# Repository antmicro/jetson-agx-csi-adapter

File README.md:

# Antmicro Jetson AGX CSI Adapter

Copyright (c) 2022-2024 [Antmicro](https://www.antmicro.com)

## Overview
This project contains hardware design files for a CSI camera adapter designed to be used with Nvidia Jetson AGX platform devkits (Orin, Xavier).
It separates the camera module interface connector into two 50-pin flat cable connectors, which are compatible with a variety of video accessories developed by Antmicro.
 
## Project structure
The main directory contains KiCad PCB project files, a LICENSE, and a README.
The remaining files are stored in the following directories:

* `img` - contains graphics for this README
* `doc` - contains generated schematics and other documentation
* `assets` - contains visual assets for showcasing this design on [Open Hardware Portal](https://openhardware.antmicro.com)

## Key features
* Nvidia Camera Module Connector compatible with Jetson AGX Orin and Jetson Xavier AGX devkits,
* Two Antmicro CSI Connectors (2x 4-lane MIPI CSI-2 or 4x 4-lane MIPI CSI-2)
* I2C multiplexer for connecting multiple cameras to separate I2C interfaces
* On-board DC-DC converter to power the cameras
* Simple frame synchronization circuitry
* QWIIC connector for external sensors
* Liquid lens connector for I2C-controlled liquid lenses

The camera connectors are electrically compatible with several video accessories created by Antmicro, such as:
 
* [Antmicro - Alvium flexible CSI adapter](https://github.com/antmicro/alvium-flexible-csi-adapter)
* [OV9281 Dual Camera Board](https://github.com/antmicro/ov9281-camera-board)
* [SDI-MIPI bridge](https://github.com/antmicro/sdi-mipi-bridge)
* [HDMI-MIPI bridge](https://github.com/antmicro/hdmi-mipi-bridge)

## License
This project is published under the [Apache-2.0](LICENSE) license.

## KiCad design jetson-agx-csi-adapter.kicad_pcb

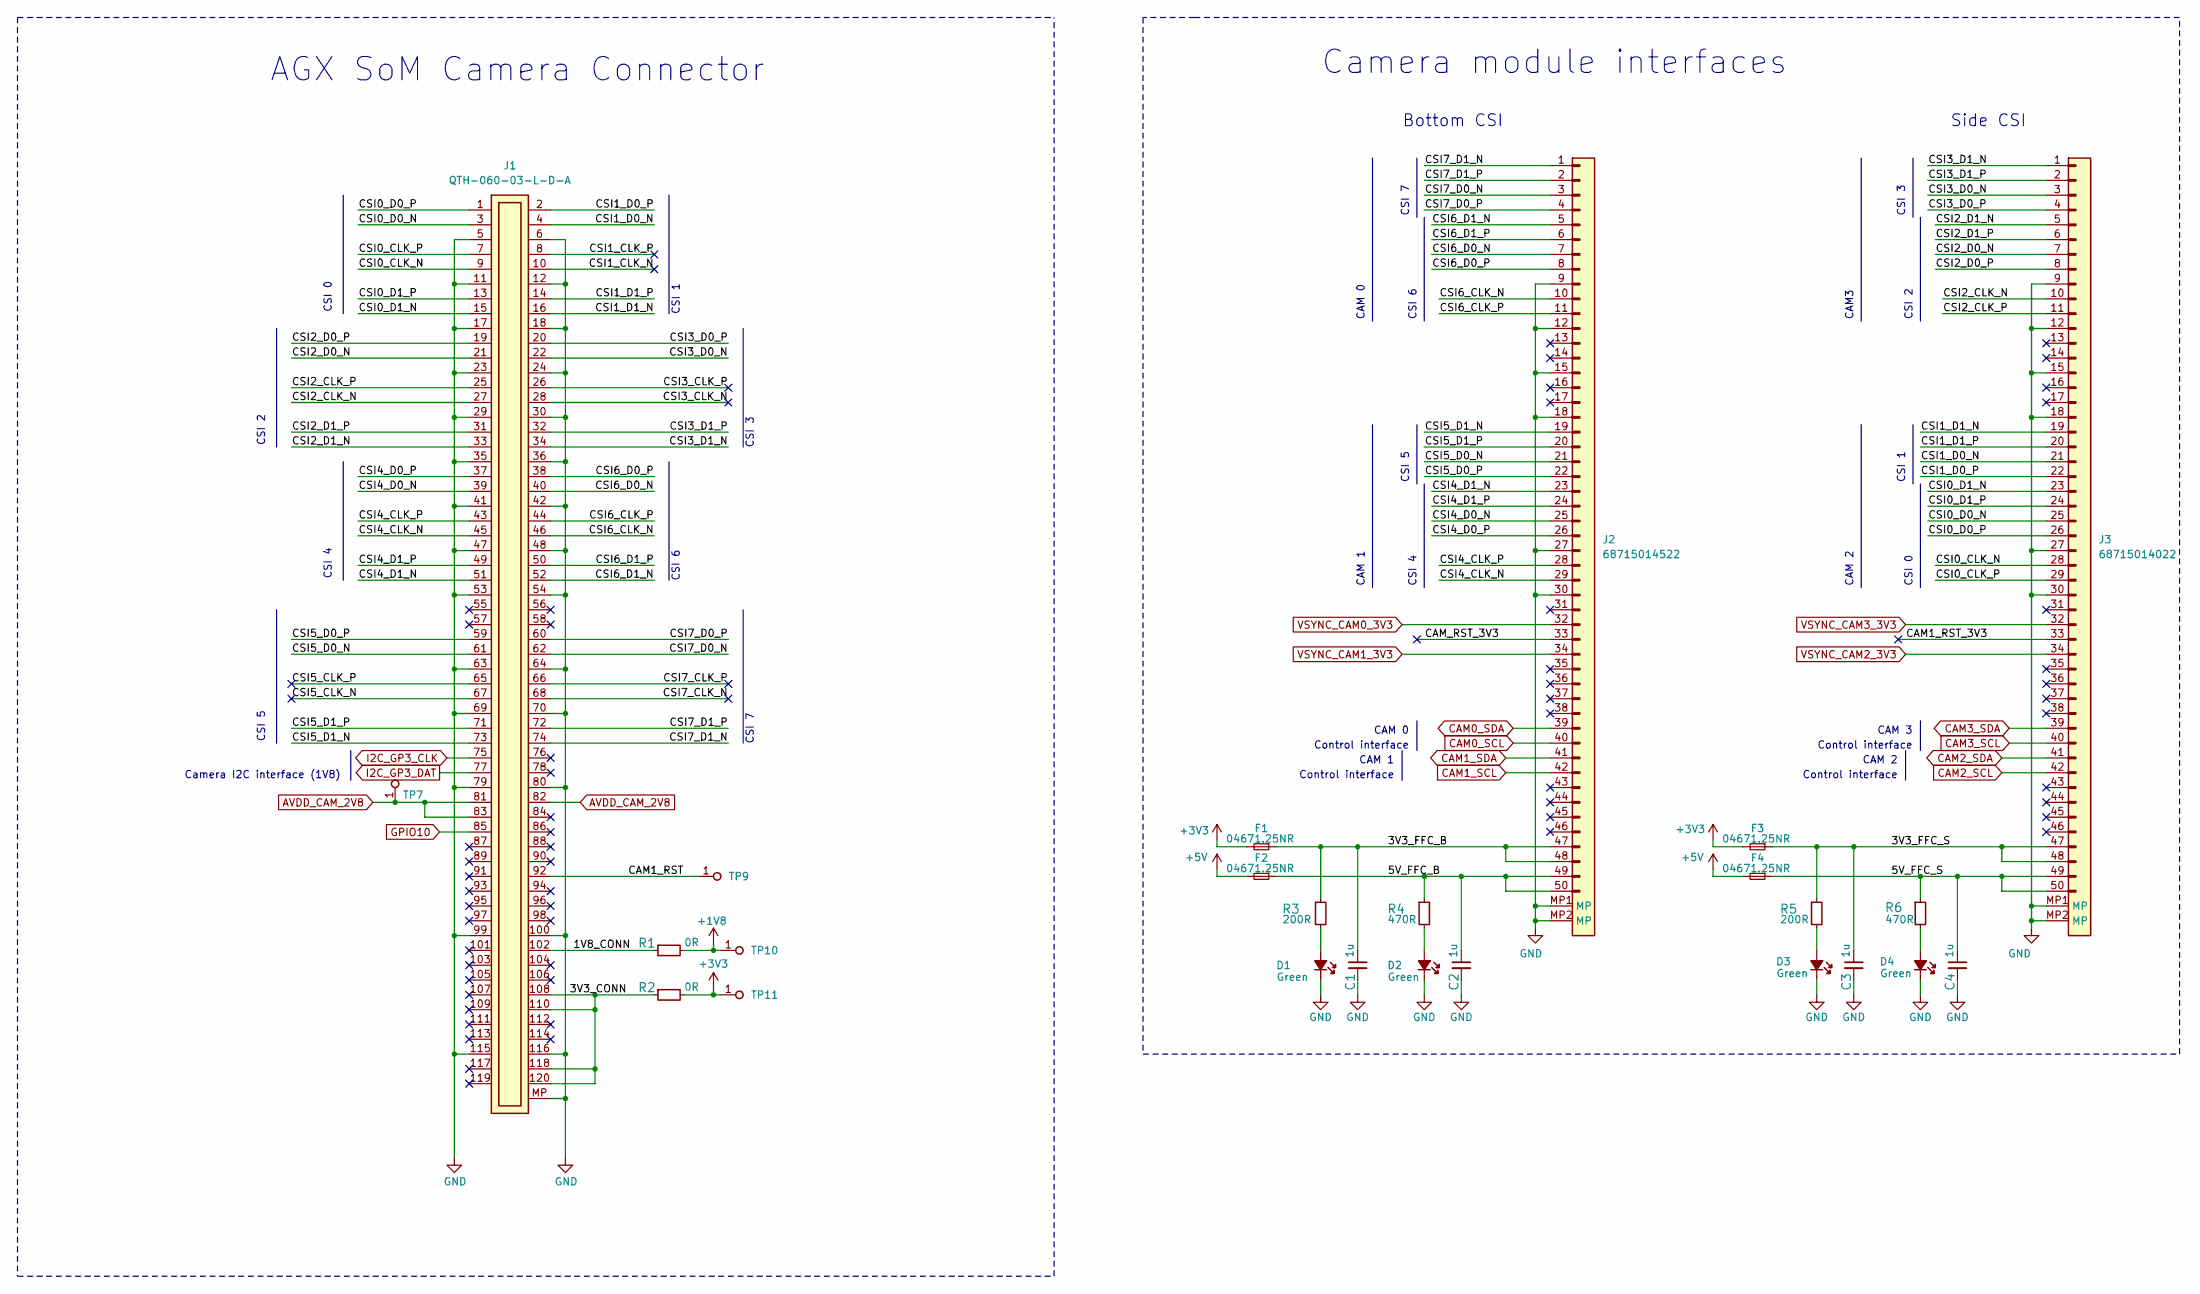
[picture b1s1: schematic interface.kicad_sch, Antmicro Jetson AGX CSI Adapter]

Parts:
C1, C2, C3, C4: C_1u_0603; C_0603_1608Metric; MPN 0603YD105KAT2A
D1, D2, D3, D4: LED_G_0603_LTST-C190GKT; LED_0603_1608Metric_G; MPN LTST-C190GKT
F1, F2, F3, F4: F_1.25A_0603; F_0603_1608Metric; MPN 04671.25NR
J1: Plug_Samtec_QTH_2x60_QTH-060-03-L-D-A; Conn_Plug_Samtec_QTH_2x60_QTH-060-03-L-D-A; MPN QTH-060-03-L-D-A
J2: Conn_FFC_WE_68715014522; Conn_FFC_WE_68715014x22; MPN 68715014522
J3: Conn_FFC_WE_68715014022_CUSTOM_FLIPPED; Conn_FFC_WE_68715014x22_CUSTOM_FLIPPED; MPN 68715014022
R1, R2: R_0R_0805; R_0805_2012Metric; MPN CRCW08050000Z0EA
R3, R5: R_200R_0402; R_0402_1005Metric; Tolerance 1%; MPN CR0402-FX-2000GLF
R4, R6: R_470R_0402; R_0402_1005Metric; Tolerance 1%; MPN CR0402-FX-4700GLF
TP7, TP9, TP10, TP11: TP_0.75mm_SMD; TP_SMD_0.75mm

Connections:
+1V8: R1.2, TP10.1; also elsewhere on the board
+3V3: F1.2, F3.2, R2.2, TP11.1; also elsewhere on the board
+5V: F2.2, F4.2; also elsewhere on the board
/Interface/1V8_CONN: J1.102, R1.1
/Interface/3V3_CONN: J1.108, J1.110, J1.118, J1.120, R2.1
/Interface/3V3_FFC_B: C1.1, F1.1, J2.47, J2.48, R3.1
/Interface/3V3_FFC_S: C3.1, F3.1, J3.47, J3.48, R5.1
/Interface/5V_FFC_B: C2.1, F2.1, J2.49, J2.50, R4.1
/Interface/5V_FFC_S: C4.1, F4.1, J3.49, J3.50, R6.1
/Interface/CAM1_RST: J1.92, TP9.1
/Interface/CAM1_RST_3V3: J3.33
/Interface/CAM_RST_3V3: J2.33
/Interface/CSI0_CLK_N: J1.9, J3.28
/Interface/CSI0_CLK_P: J1.7, J3.29
/Interface/CSI0_D0_N: J1.3, J3.25
/Interface/CSI0_D0_P: J1.1, J3.26
/Interface/CSI0_D1_N: J1.15, J3.23
/Interface/CSI0_D1_P: J1.13, J3.24
/Interface/CSI1_CLK_N: J1.10
/Interface/CSI1_CLK_P: J1.8
/Interface/CSI1_D0_N: J1.4, J3.21
/Interface/CSI1_D0_P: J1.2, J3.22
/Interface/CSI1_D1_N: J1.16, J3.19
/Interface/CSI1_D1_P: J1.14, J3.20
/Interface/CSI2_CLK_N: J1.27, J3.10
/Interface/CSI2_CLK_P: J1.25, J3.11
/Interface/CSI2_D0_N: J1.21, J3.7
/Interface/CSI2_D0_P: J1.19, J3.8
/Interface/CSI2_D1_N: J1.33, J3.5
/Interface/CSI2_D1_P: J1.31, J3.6
/Interface/CSI3_CLK_N: J1.28
/Interface/CSI3_CLK_P: J1.26
/Interface/CSI3_D0_N: J1.22, J3.3
/Interface/CSI3_D0_P: J1.20, J3.4
/Interface/CSI3_D1_N: J1.34, J3.1
/Interface/CSI3_D1_P: J1.32, J3.2
/Interface/CSI4_CLK_N: J1.45, J2.29
/Interface/CSI4_CLK_P: J1.43, J2.28
/Interface/CSI4_D0_N: J1.39, J2.25
/Interface/CSI4_D0_P: J1.37, J2.26
/Interface/CSI4_D1_N: J1.51, J2.23
/Interface/CSI4_D1_P: J1.49, J2.24
/Interface/CSI5_CLK_N: J1.67
/Interface/CSI5_CLK_P: J1.65
/Interface/CSI5_D0_N: J1.61, J2.21
/Interface/CSI5_D0_P: J1.59, J2.22
/Interface/CSI5_D1_N: J1.73, J2.19
/Interface/CSI5_D1_P: J1.71, J2.20
/Interface/CSI6_CLK_N: J1.46, J2.10
/Interface/CSI6_CLK_P: J1.44, J2.11
/Interface/CSI6_D0_N: J1.40, J2.7
/Interface/CSI6_D0_P: J1.38, J2.8
/Interface/CSI6_D1_N: J1.52, J2.5
/Interface/CSI6_D1_P: J1.50, J2.6
/Interface/CSI7_CLK_N: J1.68
/Interface/CSI7_CLK_P: J1.66
/Interface/CSI7_D0_N: J1.62, J2.3
/Interface/CSI7_D0_P: J1.60, J2.4
/Interface/CSI7_D1_N: J1.74, J2.1
/Interface/CSI7_D1_P: J1.72, J2.2
AVDD_CAM_2V8: J1.81, J1.82, J1.83, TP7.1
CAM0_SCL: J2.40; also elsewhere on the board
CAM0_SDA: J2.39; also elsewhere on the board
CAM1_SCL: J2.42; also elsewhere on the board
CAM1_SDA: J2.41; also elsewhere on the board
CAM2_SCL: J3.42; also elsewhere on the board
CAM2_SDA: J3.41; also elsewhere on the board
CAM3_SCL: J3.40; also elsewhere on the board
CAM3_SDA: J3.39; also elsewhere on the board
GND: C1.2, C2.2, C3.2, C4.2, D1.1 (C), D2.1 (C), D3.1 (C), D4.1 (C), J1.5, J1.6, J1.11, J1.12, J1.17, J1.18, J1.23, J1.24, J1.29, J1.30, J1.35, J1.36, J1.41, J1.42, J1.47, J1.48, J1.53, J1.54, J1.63, J1.64, J1.69, J1.70, J1.79, J1.80, J1.99, J1.100, J1.115, J1.116, J1.MP, J2.9, J2.12, J2.15, J2.18, J2.27, J2.30, J2.MP1 (MP), J2.MP2 (MP), J3.9, J3.12, J3.15, J3.18, J3.27, J3.30, J3.MP1 (MP), J3.MP2 (MP); also elsewhere on the board
GPIO10: J1.85; also elsewhere on the board
I2C_GP3_CLK: J1.75; also elsewhere on the board
I2C_GP3_DAT: J1.77; also elsewhere on the board
unnamed: D1.2 (A), R3.2
unnamed: D2.2 (A), R4.2
unnamed: D3.2 (A), R5.2
unnamed: D4.2 (A), R6.2
VSYNC_CAM0_3V3: J2.32; also elsewhere on the board
VSYNC_CAM1_3V3: J2.34; also elsewhere on the board
VSYNC_CAM2_3V3: J3.34; also elsewhere on the board
VSYNC_CAM3_3V3: J3.32; also elsewhere on the board

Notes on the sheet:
CSI 1
AGX SoM Camera Connector
CAM 0
CAM 2
CSI 4
Control interface
Camera module interfaces
CAM 1
CSI 6
CSI 7
CSI 0
CSI 5
Bottom CSI
CSI 3
CSI 2
CAM 3
Side CSI
CAM3
Camera I2C interface (1V8)

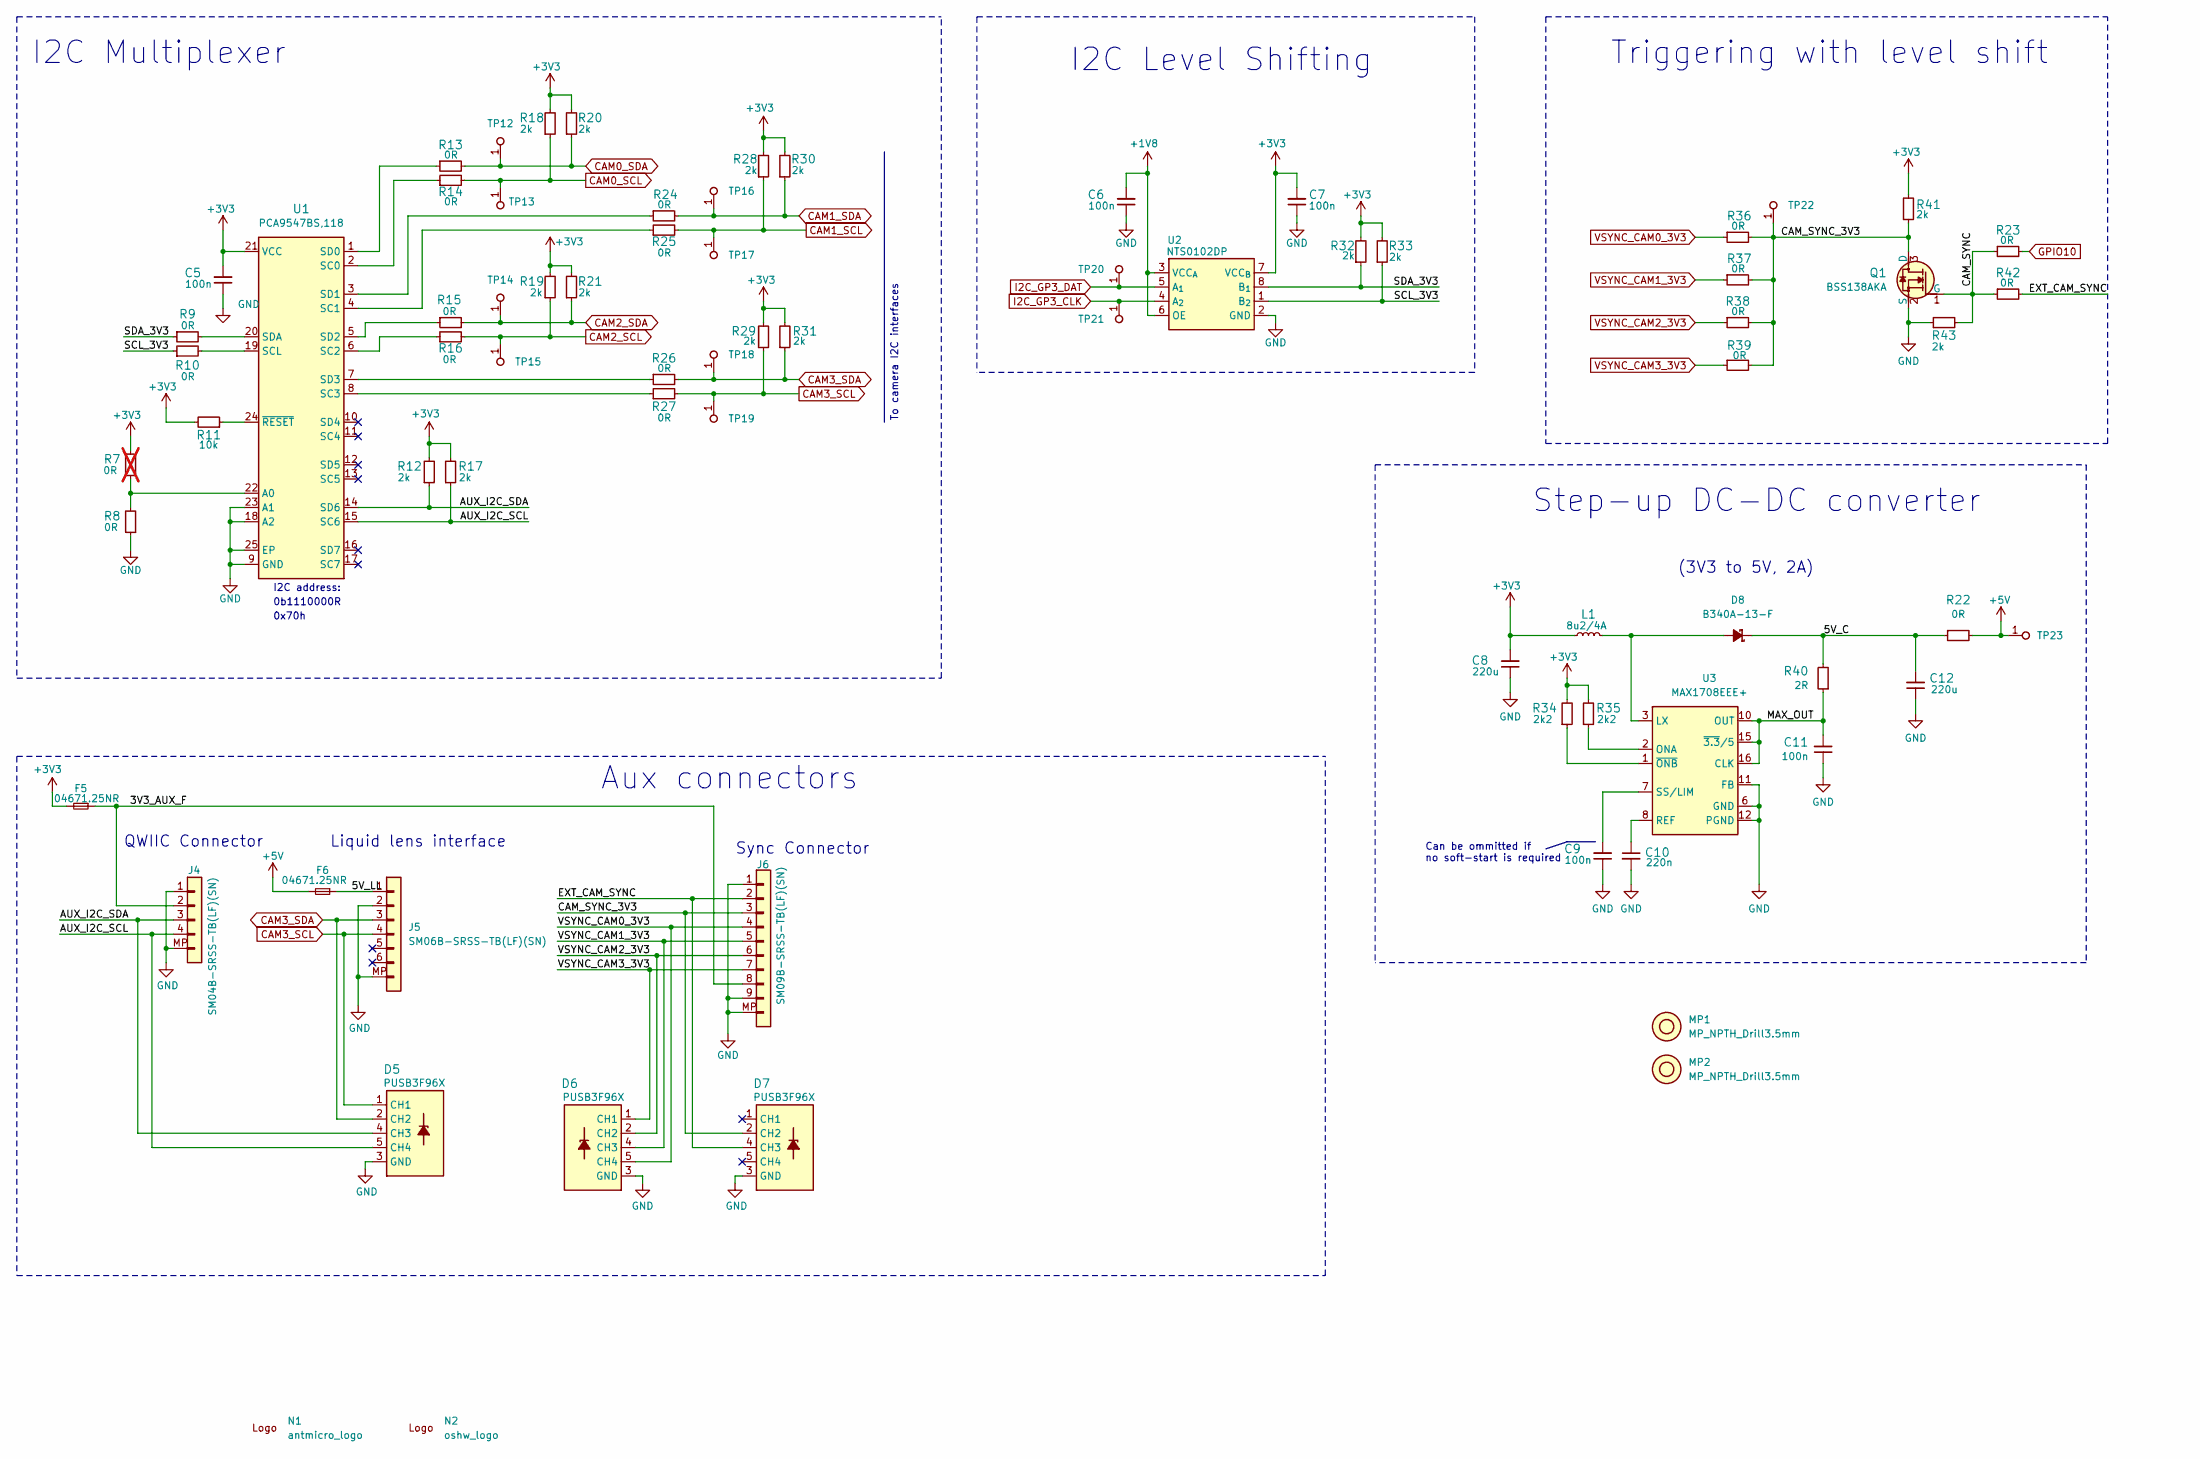
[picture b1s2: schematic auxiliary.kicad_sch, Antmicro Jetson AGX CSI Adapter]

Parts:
C5, C6, C7: C_100n_0402; C_0402_1005Metric; Voltage 50V; MPN GRM155R61H104KE14D
C8, C12: C_220u_1206_6V3; C_1206_3216Metric; MPN GRM31CR60J227ME11L
C9, C11: C_100n_0603; C_0603_1608Metric; MPN 0603YC104KAZ2A
C10: C_220n_0603; C_0603_1608Metric; MPN 0603B224K100CT
D5, D6, D7: PUSB3F96X_PASS; Nexperia_DFN-10_2.5x1mm_P0.5mm; MPN PUSB3F96X
D8: B340A-13-F; D_SMA; MPN B340A-13-F
F5, F6: F_1.25A_0603; F_0603_1608Metric; MPN 04671.25NR
J4: JST_SH_1x4_SM04B-SRSS-TB-LF-SN; Conn_JST_SH_1x4_SM04B-SRSS-TB-LF-SN; MPN SM04B-SRSS-TB(LF)(SN)
J5: JST_SH_1x6_SM06B-SRSS-TB-LF-SN; Conn_JST_SH_1x6_SM06B-SRSS-TB-LF-SN; MPN SM06B-SRSS-TB(LF)(SN)
J6: JST_SH_1x9_SM09B-SRSS-TB-LF-SN; Conn_JST_SH_1x9_SM09B-SRSS-TB-LF-SN; MPN SM09B-SRSS-TB(LF)(SN)
L1: L_8u2_4A_2525; L_2525_6363Metric; MPN IHLP2525CZER8R2M01
MP1, MP2: MP_NPTH_Drill3.5mm
N1: antmicro_logo; antmicro-logo_scaled_20mm
N2: oshw_logo; oshw-logo
Q1: BSS138AKA; SOT-23-3; MPN BSS138AKA
R7: R_0R_0402; R_0402_1005Metric; MPN ERJ2GE0R00X; not fitted
R8, R9, R10, R13, R14, R15, R16, R23, R24, R25, R26, R27, R36, R37, R38, R39, R42: R_0R_0402; R_0402_1005Metric; MPN ERJ2GE0R00X
R11: R_10k_0402; R_0402_1005Metric; Tolerance 1%; MPN CR0402-FX-1002GLF
R12, R17, R18, R19, R20, R21, R28, R29, R30, R31, R32, R33, R41, R43: R_2k_0402; R_0402_1005Metric; Tolerance 1%; MPN CR0402-FX-2001GLF
R22: R_0R_0805; R_0805_2012Metric; MPN CRCW08050000Z0EA
R34, R35: R_2k2_0603; R_0603_1608Metric; Tolerance 1%; MPN CR0603-FX-2201ELF
R40: R_2R_0603; R_0603_1608Metric; Tolerance 1%; MPN CR0603-FX-2R00ELF
TP12, TP13, TP14, TP15, TP16, TP17, TP18, TP19, TP20, TP21, TP22, TP23: TP_0.75mm_SMD; TP_SMD_0.75mm
U1: PCA9547_VQFN; VQFN-24-1EP_3.8x3.8x1.0mm_P0.5mm; MPN PCA9547BS,118
U2: NTS0102_TSSOP; TSSOP-8_3x3mm_P0.65mm; MPN NTS0102DP
U3: MAX1708EEE+; QSOP-16_3.9x4.9mm_P0.635mm; MPN MAX1708EEE+

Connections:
+1V8: C6.2, U2.3 (VCC_{A}), U2.6 (OE); also elsewhere on the board
+3V3: C5.2, C7.2, C8.2, F5.2, L1.1, R7.2, R11.2, R12.2, R17.2, R18.2, R19.2, R20.2, R21.2, R28.2, R29.2, R30.2, R31.2, R32.2, R33.2, R34.2, R35.2, R41.2, U1.21 (VCC), U2.7 (VCC_{B}); also elsewhere on the board
+5V: F6.2, R22.2, TP23.1; also elsewhere on the board
/Auxiliary/3V3_AUX_F: F5.1, J4.2, J6.8
/Auxiliary/5V_C: C12.2, D8.1 (C), R22.1, R40.2
/Auxiliary/5V_LL: F6.1, J5.1
/Auxiliary/AUX_I2C_SCL: D5.5 (CH4), D5.6 (CH4), J4.4, R17.1, U1.15 (SC6)
/Auxiliary/AUX_I2C_SDA: D5.4 (CH3), D5.7 (CH3), J4.3, R12.1, U1.14 (SD6)
/Auxiliary/CAM_SYNC: Q1.1 (G), R23.1, R42.1, R43.2
/Auxiliary/CAM_SYNC_3V3: D7.2 (CH2), D7.9 (CH2), J6.3, Q1.3 (D), R36.2, R37.2, R38.2, R39.2, R41.1, TP22.1
/Auxiliary/EXT_CAM_SYNC: D7.4 (CH3), D7.7 (CH3), J6.2, R42.2
/Auxiliary/MAX_OUT: C11.2, R40.1, U3.10 (OUT), U3.15 (~3.3/5), U3.16 (CLK)
/Auxiliary/SCL_3V3: R10.1, R33.1, U2.1 (B_{2})
/Auxiliary/SDA_3V3: R9.1, R32.1, U2.8 (B_{1})
CAM0_SCL: R14.2, R18.1, TP13.1; also elsewhere on the board
CAM0_SDA: R13.2, R20.1, TP12.1; also elsewhere on the board
CAM1_SCL: R25.2, R28.1, TP17.1; also elsewhere on the board
CAM1_SDA: R24.2, R30.1, TP16.1; also elsewhere on the board
CAM2_SCL: R16.2, R19.1, TP15.1; also elsewhere on the board
CAM2_SDA: R15.2, R21.1, TP14.1; also elsewhere on the board
CAM3_SCL: D5.1 (CH1), D5.10 (CH1), J5.4, R27.2, R29.1, TP19.1; also elsewhere on the board
CAM3_SDA: D5.2 (CH2), D5.9 (CH2), J5.3, R26.2, R31.1, TP18.1; also elsewhere on the board
GND: C5.1, C6.1, C7.1, C8.1, C9.1, C10.2, C11.1, C12.1, D5.3 (GND), D5.8 (GND), D6.3 (GND), D6.8 (GND), D7.3 (GND), D7.8 (GND), J4.1, J4.MP, J5.2, J5.MP, J6.1, J6.9, J6.MP, Q1.2 (S), R8.1, R43.1, U1.9 (GND), U1.18 (A2), U1.23 (A1), U1.25 (EP), U2.2 (GND), U3.6 (GND), U3.9 (GND), U3.11 (FB), U3.12 (PGND), U3.13 (PGND), U3.14 (PGND); also elsewhere on the board
GPIO10: R23.2; also elsewhere on the board
I2C_GP3_CLK: TP21.1, U2.4 (A_{2}); also elsewhere on the board
I2C_GP3_DAT: TP20.1, U2.5 (A_{1}); also elsewhere on the board
unnamed: D8.2 (A), L1.2, U3.3 (LX), U3.4 (LX), U3.5 (LX)
unnamed: R7.1, R8.2, U1.22 (A0)
unnamed: R14.1, U1.2 (SC0)
unnamed: R25.1, U1.4 (SC1)
unnamed: R16.1, U1.6 (SC2)
unnamed: R27.1, U1.8 (SC3)
unnamed: R10.2, U1.19 (SCL)
unnamed: R13.1, U1.1 (SD0)
unnamed: R24.1, U1.3 (SD1)
unnamed: R15.1, U1.5 (SD2)
unnamed: R26.1, U1.7 (SD3)
unnamed: R9.2, U1.20 (SDA)
unnamed: R11.1, U1.24 (~RESET)
unnamed: R35.1, U3.2 (ONA)
unnamed: C10.1, U3.8 (REF)
unnamed: C9.2, U3.7 (SS/LIM)
unnamed: R34.1, U3.1 (~ONB)
VSYNC_CAM0_3V3: D6.5 (CH4), D6.6 (CH4), J6.4, R36.1; also elsewhere on the board
VSYNC_CAM1_3V3: D6.4 (CH3), D6.7 (CH3), J6.5, R37.1; also elsewhere on the board
VSYNC_CAM2_3V3: D6.2 (CH2), D6.9 (CH2), J6.6, R38.1; also elsewhere on the board
VSYNC_CAM3_3V3: D6.1 (CH1), D6.10 (CH1), J6.7, R39.1; also elsewhere on the board

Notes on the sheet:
(3V3 to 5V, 2A)
Can be ommitted if no soft-start is required
I2C address:
0x70h
Liquid lens interface
Triggering with level shift
QWIIC Connector
Step-up DC-DC converter
0b1110000R
I2C Level Shifting
Sync Connector
To camera I2C interfaces
Aux connectors
I2C Multiplexer

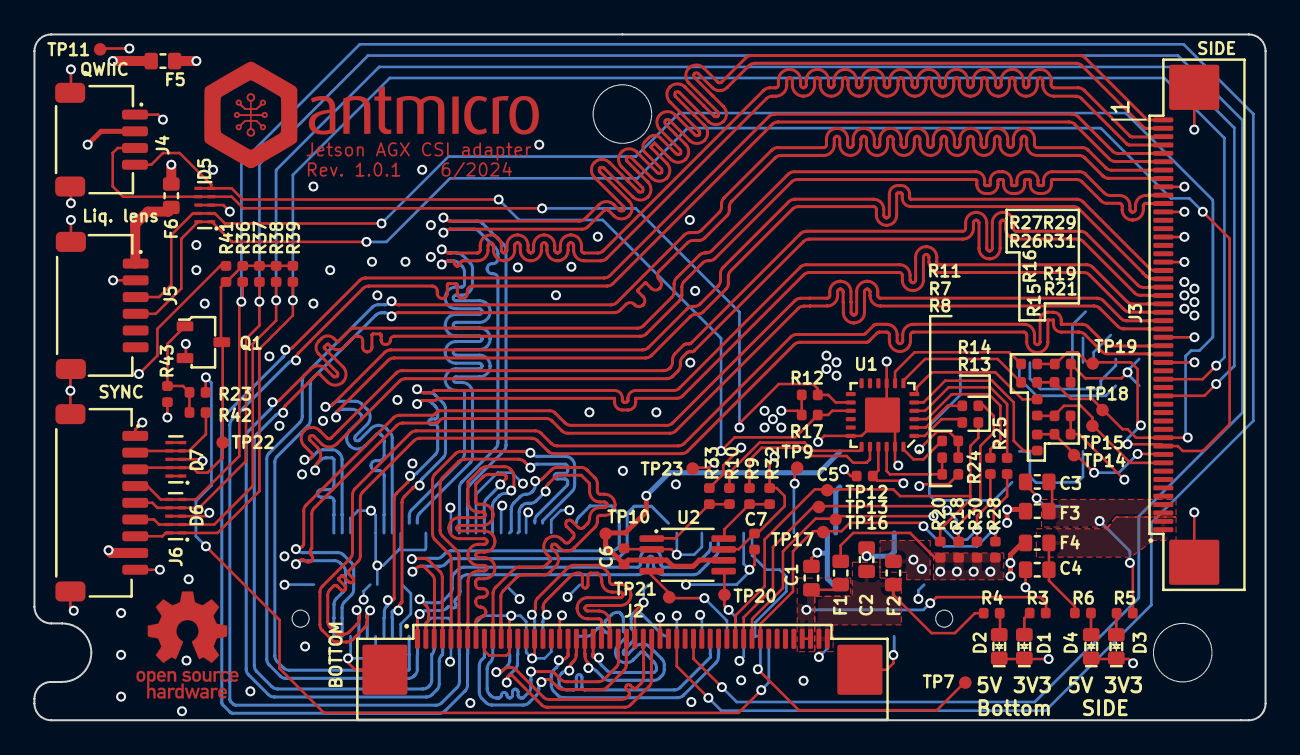
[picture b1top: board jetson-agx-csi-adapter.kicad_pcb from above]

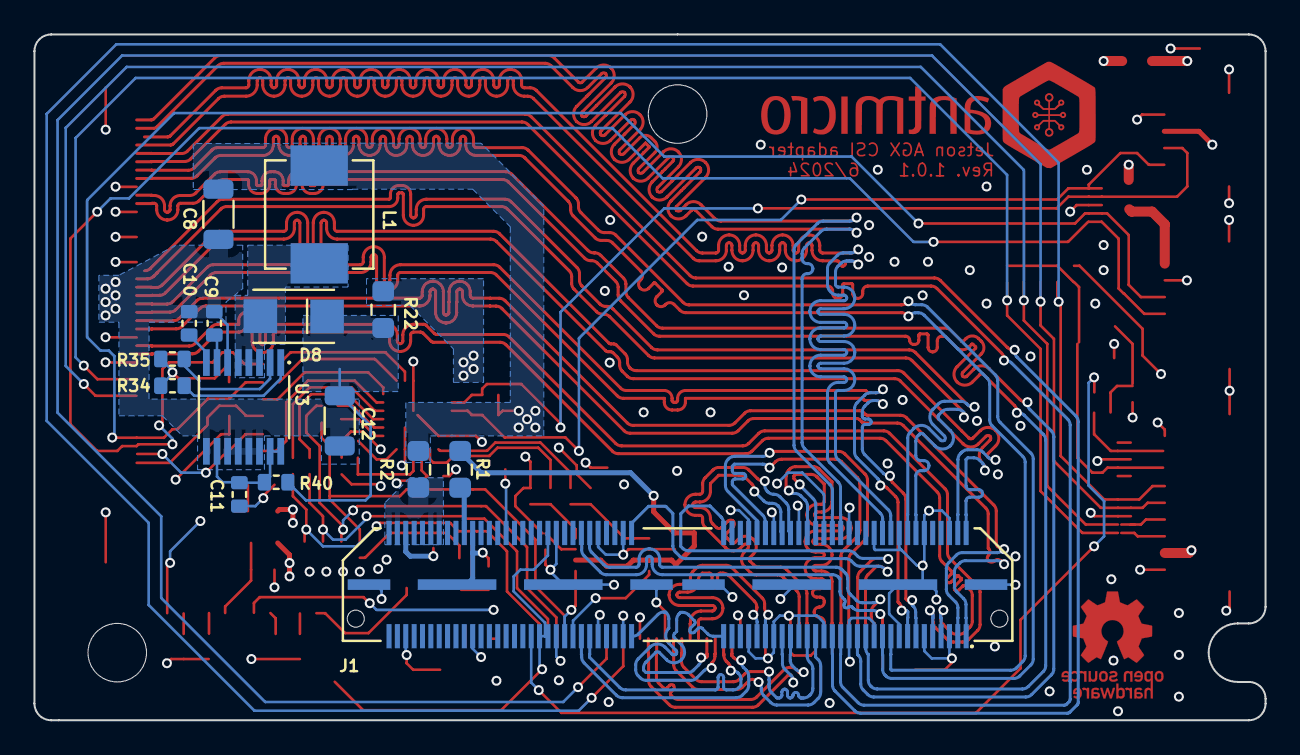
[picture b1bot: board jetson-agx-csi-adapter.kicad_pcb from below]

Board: 4 copper layers, 73.6 x 41.0 mm, 100 parts (15 on the bottom side), 99 nets.

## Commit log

2022-07-27 Removed AUX connector and changed SYNC connector package
2022-07-27 Add logos
2022-07-27 Fixed length matching
2022-07-27 Finished layout of most of the other signals, rerouted CSI
2022-07-27 Created readme
2022-07-27 Fixed sync pin naming
2022-07-27 Started PCB layout
2022-07-27 Filleted CSI tracks
2022-07-27 Fixed adapter types
2022-07-27 Routed CSI interface
2022-07-27 Added maximum height of components and fixed connector footprint on mockup pcb
2022-07-27 Prototyping EC E1434730
2022-07-27 Add license
2022-07-27 Length matched CSI signals
2022-07-27 Replaced some components with larger package, routed more signals
2022-07-27 Fixes suggested in review
2022-07-27 Merged zones and minor net fixes
2022-07-27 More changes from review
2022-07-27 Added PCB outline
2022-07-27 Fixed bottom silkscreen
2022-07-27 Swapped QWIIC connector to a side entry one
2022-07-27 Changed pinout to match Jetson Nano Baseboard
2022-07-27 Add TVS to wire connectors
2022-07-27 Cleaned up silk screen
2022-07-27 Added logos and changed top and bottom side
2022-07-27 Added fuses for aux connectors
2022-07-27 Changed 5V converter capacitors to ceramic for lower ESR
2022-07-27 Routed all the signals
2022-07-27 Rerouted tracks after connector change
2022-07-27 Routed I2C signals, completed a layout of the voltage converter and I2C IC.
2022-07-27 Added loclib, updated README and added pdf schematic
2022-08-18 README: Add photo
2022-09-22 Notes added by 'git notes add'
2022-10-24 Remove redundant sheet
2023-03-31 README: minor fixes, add OSP link
2024-06-14 [#60956] WiP Update symbols references
2024-06-14 [#60956] WiP Update footprints
2024-06-14 [#60956] Allign designators
2024-06-18 [#60956] Update B340A-13-F,MAX1708EEE+ and TP_0_75mm from library
2024-06-18 [#60956] Allign PCB with SCH changes
2024-06-18 [#60956] Bump rev to 1.0.1
2024-06-20 [#60956] Update Max1708 after component rev
2024-06-24 [#60956] Upload assets
2024-06-24 [#60956] Clear DRCs
2024-06-24 [#60956] Switch kibuzzard text fields to knockouts
2024-06-24 [#60956] Set DRC exclusions
2024-06-24 [#60956] Update dates
2024-06-25 [#60956] Update assets
2024-06-26 [#60956] Remove antmicro prefix from board name
2024-06-26 [#60956] Remove lib folder
2024-06-26 [#60956] Upload stackup.csv
2024-06-28 [#60956] Update README
2025-12-09 [#84630] Project refresh 81589

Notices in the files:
parts and their libraries:
License: Apache-2.0
